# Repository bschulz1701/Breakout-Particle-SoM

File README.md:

# Breakout_Particle-SoM
Breakout board to adapt the Particle SoM system to the established Feather form-factor

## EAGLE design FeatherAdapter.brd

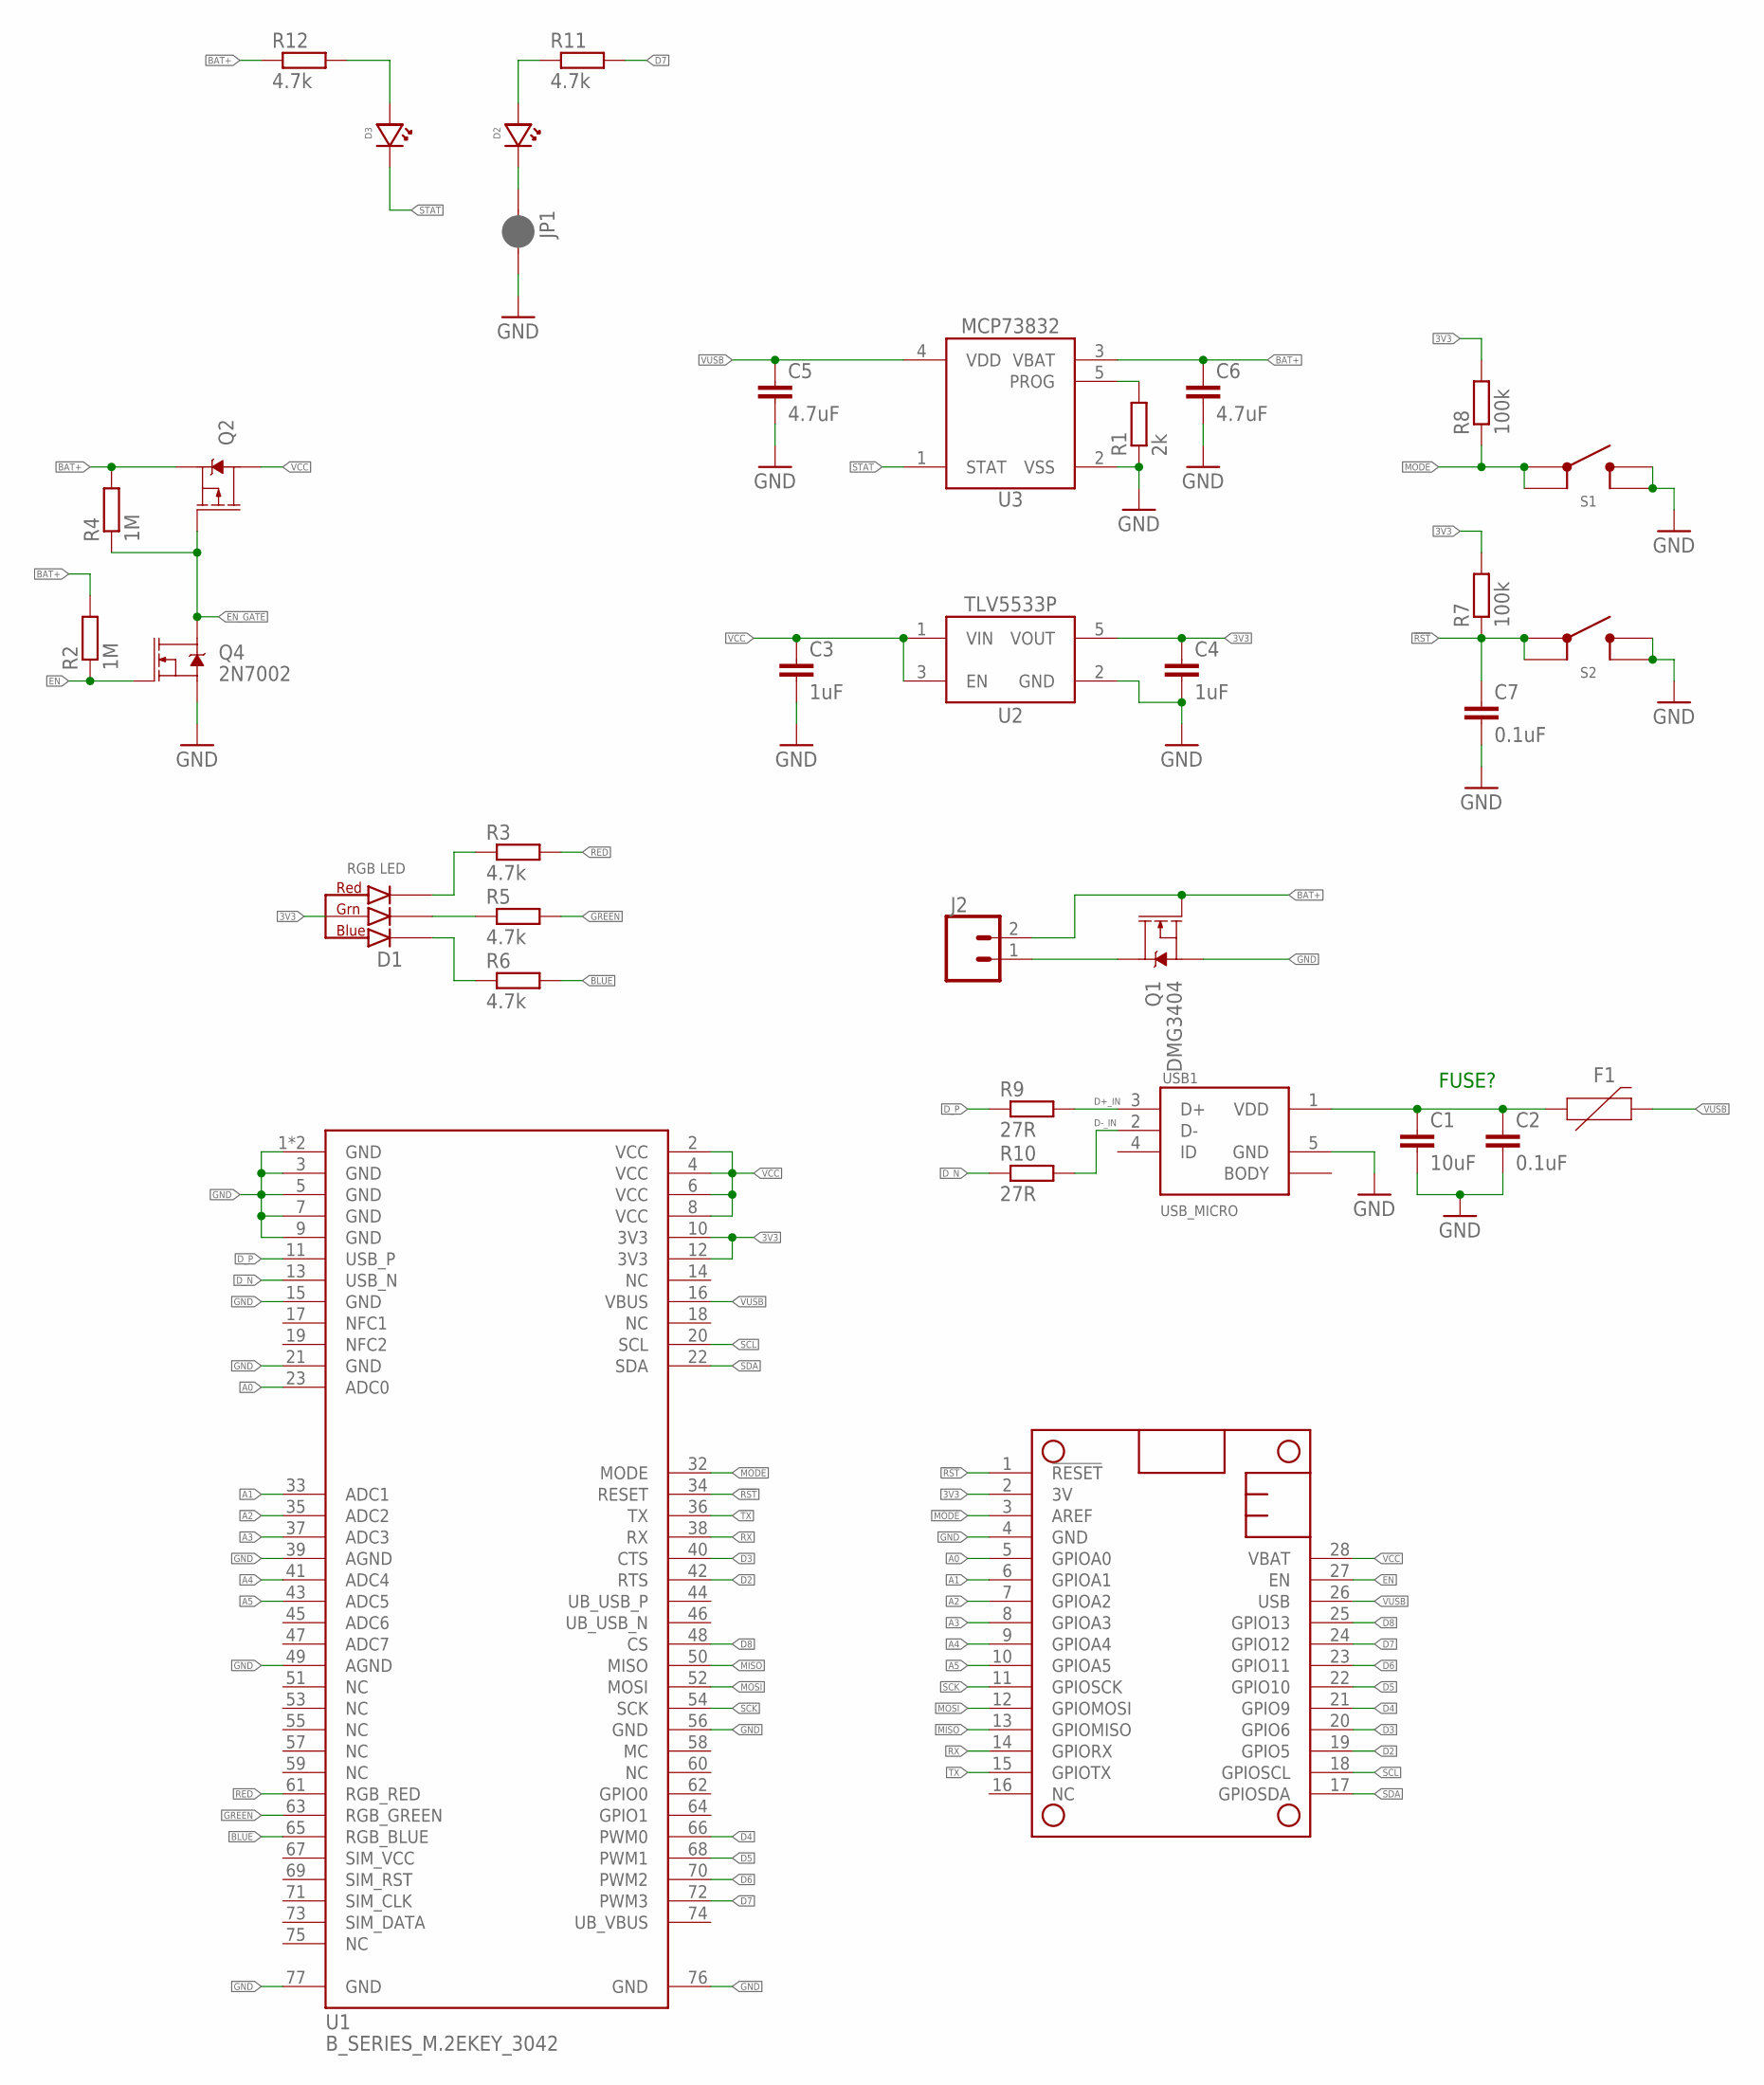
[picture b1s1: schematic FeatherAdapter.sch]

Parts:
C1: 10uF; C0805
C2, C7: 0.1uF; C0402
C3, C4: 1uF; C0603
C5, C6: 4.7uF; C0805
D1: CLVBA-FKA
D2: LEDBLUE0603; LED_0603
D3: LEDAMBER0603; LED_0603
F1: PPTC1.5A; 1206
J2: CONN_02-JST-2MM-SMT; JST-2-SMD
JP1: JUMPER-SMT_2_NC_PASTE_SILK_ROUND; SMT-JUMPER_2_NC_SILK_ROUND
MS1: FEATHERWING_SMD_LAYOUT; FEATHER_SMD_MIN
Q1: DMG3404; SOT23-3
Q2: NX2301P; SOT23-3
Q4: 2N7002; SOT23-3
R1: 2k; R0402
R2, R4: 1M; R0402
R3, R5, R6, R11, R12: 4.7k; R0402
R7, R8: 100k; R0402
R9, R10: 27R; R0402
S1, S2: BUTTON4.5X4.5; SWITCH_4.5MM
U1: B_SERIES_M.2EKEY_3042; PARTICLE_M.2EKEY
U2: TLV755P3V3SOT23; DBV0005A
U3: MCP73832SOT; SOT23-5
USB1: USB_MICRO; 10118194-0001LF_10118194-0001LF_LONGER_PADS

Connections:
3V3: C4.1, D1.2 (ANODE), MS1.2 (3V), R7.2, R8.2, U1.10 (3V3), U1.12 (3V3), U2.5 (VOUT)
!RST: C7.1, MS1.1 (!RESET), R7.1, S2.1, S2.2, U1.34 (RESET)
A0: MS1.5 (GPIOA0), U1.23 (ADC0)
A1: MS1.6 (GPIOA1), U1.33 (ADC1)
A2: MS1.7 (GPIOA2), U1.35 (ADC2)
A3: MS1.8 (GPIOA3), U1.37 (ADC3)
A4: MS1.9 (GPIOA4), U1.41 (ADC4)
A5: MS1.10 (GPIOA5), U1.43 (ADC5)
BAT+: C6.1, J2.2 (1), Q1.1 (G), Q2.2 (S), R2.2, R4.2, R12.1, U3.3 (VBAT)
BAT-: J2.1 (2), Q1.3 (D)
BLUE: R6.2, U1.65 (RGB_BLUE)
D2: MS1.19 (GPIO5), U1.42 (RTS)
D3: MS1.20 (GPIO6), U1.40 (CTS)
D4: MS1.21 (GPIO9), U1.66 (PWM0)
D5: MS1.22 (GPIO10), U1.68 (PWM1)
D6: MS1.23 (GPIO11), U1.70 (PWM2)
D7: MS1.24 (GPIO12), R11.2, U1.72 (PWM3)
D8: MS1.25 (GPIO13), U1.48 (CS)
D+_IN: R9.2, USB1.3 (D+)
D-_IN: R10.2, USB1.2 (D-)
D_N: R10.1, U1.13 (USB_N)
D_P: R9.1, U1.11 (USB_P)
EN: MS1.27 (EN), Q4.1 (G), R2.1
EN_GATE: Q2.1 (G), Q4.3 (D), R4.1
GND: C1.2, C2.2, C3.2, C4.2, C5.2, C6.2, C7.2, JP1.2, MS1.4 (GND), Q1.2 (S), Q4.2 (S), R1.1, S1.3, S1.4, S2.3, S2.4, U1.1 (GND), U1.3 (GND), U1.5 (GND), U1.7 (GND), U1.9 (GND), U1.15 (GND), U1.21 (GND), U1.39 (AGND), U1.49 (AGND), U1.56 (GND), U1.76 (GND), U1.77 (GND), U1.GND, U2.2 (GND), U3.2 (VSS), USB1.5 (GND)
GREEN: R5.2, U1.63 (RGB_GREEN)
MISO: MS1.13 (GPIOMISO), U1.50 (MISO)
MODE: MS1.3 (AREF), R8.1, S1.1, S1.2, U1.32 (MODE)
MOSI: MS1.12 (GPIOMOSI), U1.52 (MOSI)
unnamed: R1.2, U3.5 (PROG)
unnamed: C1.1, C2.1, F1.1, USB1.1 (VDD)
unnamed: D2.CATHODE, JP1.1
unnamed: D1.1 (RED_CATH), R3.1
unnamed: D1.4 (GREEN_CATH), R5.1
unnamed: D1.3 (BLUE_CATH), R6.1
unnamed: D2.ANODE, R11.1
unnamed: D3.ANODE, R12.2
RED: R3.2, U1.61 (RGB_RED)
RX: MS1.14 (GPIORX), U1.38 (RX)
SCK: MS1.11 (GPIOSCK), U1.54 (SCK)
SCL: MS1.18 (GPIOSCL), U1.20 (SCL)
SDA: MS1.17 (GPIOSDA), U1.22 (SDA)
SIM_VCC: U1.67 (SIM_VCC)
STAT: D3.CATHODE, U3.1 (STAT)
TX: MS1.15 (GPIOTX), U1.36 (TX)
UB_VBUS: U1.74 (UB_VBUS)
VCC: C3.1, MS1.28 (VBAT), Q2.3 (D), U1.2 (VCC), U1.4 (VCC), U1.6 (VCC), U1.8 (VCC), U2.1 (VIN), U2.3 (EN)
VUSB: C5.1, F1.2, MS1.26 (USB), U1.16 (VBUS), U3.4 (VDD)

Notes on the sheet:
FUSE?

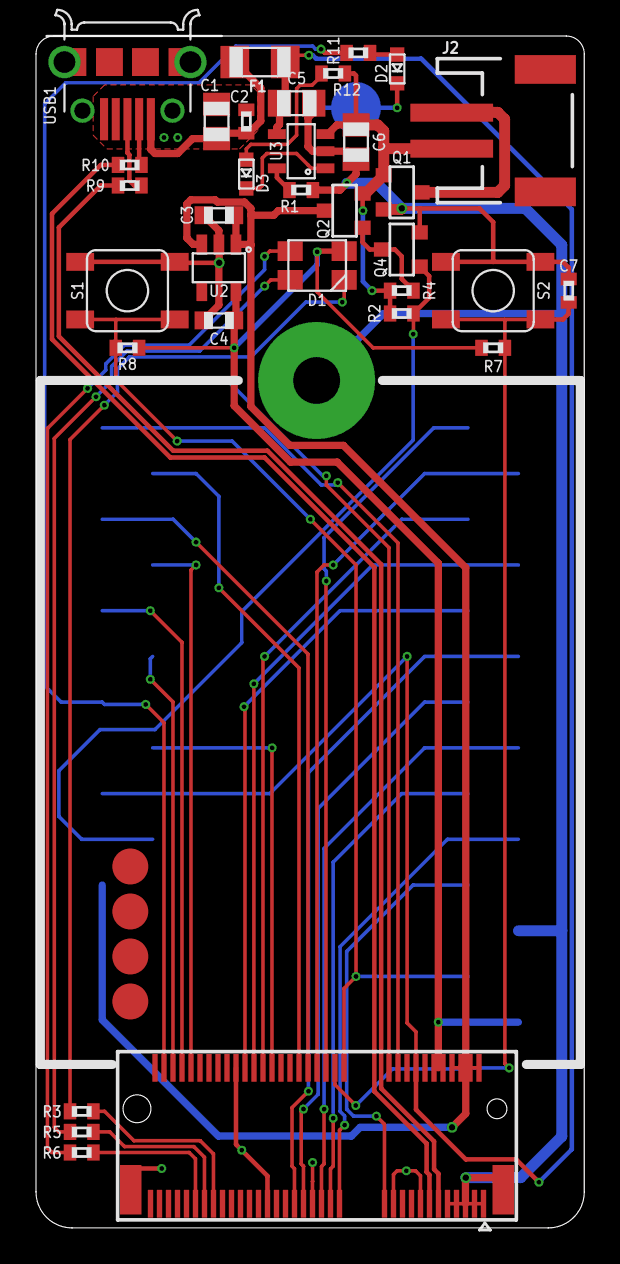
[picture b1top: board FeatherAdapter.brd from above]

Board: 2 copper layers, 30.5 x 66.2 mm, 35 parts (1 on the bottom side), 46 nets.

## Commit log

2024-09-18 Added LICENSE
2024-09-20 Partial schematic capture
2024-09-20 Continued schematic capture
2024-09-23 Further schematic capture
2024-09-25 Board component placement
2024-09-26 Initial layout

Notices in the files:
parts and their libraries:
Particle-Devices: Licensing: Designed by Particle.
